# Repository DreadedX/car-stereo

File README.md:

# Peugeot 207 Bluetooth music receiver
My Peugeot has bluetooth, but only for calling.
This project aims to build a bluetooth receiver to attached to the aux in in the glovebox.

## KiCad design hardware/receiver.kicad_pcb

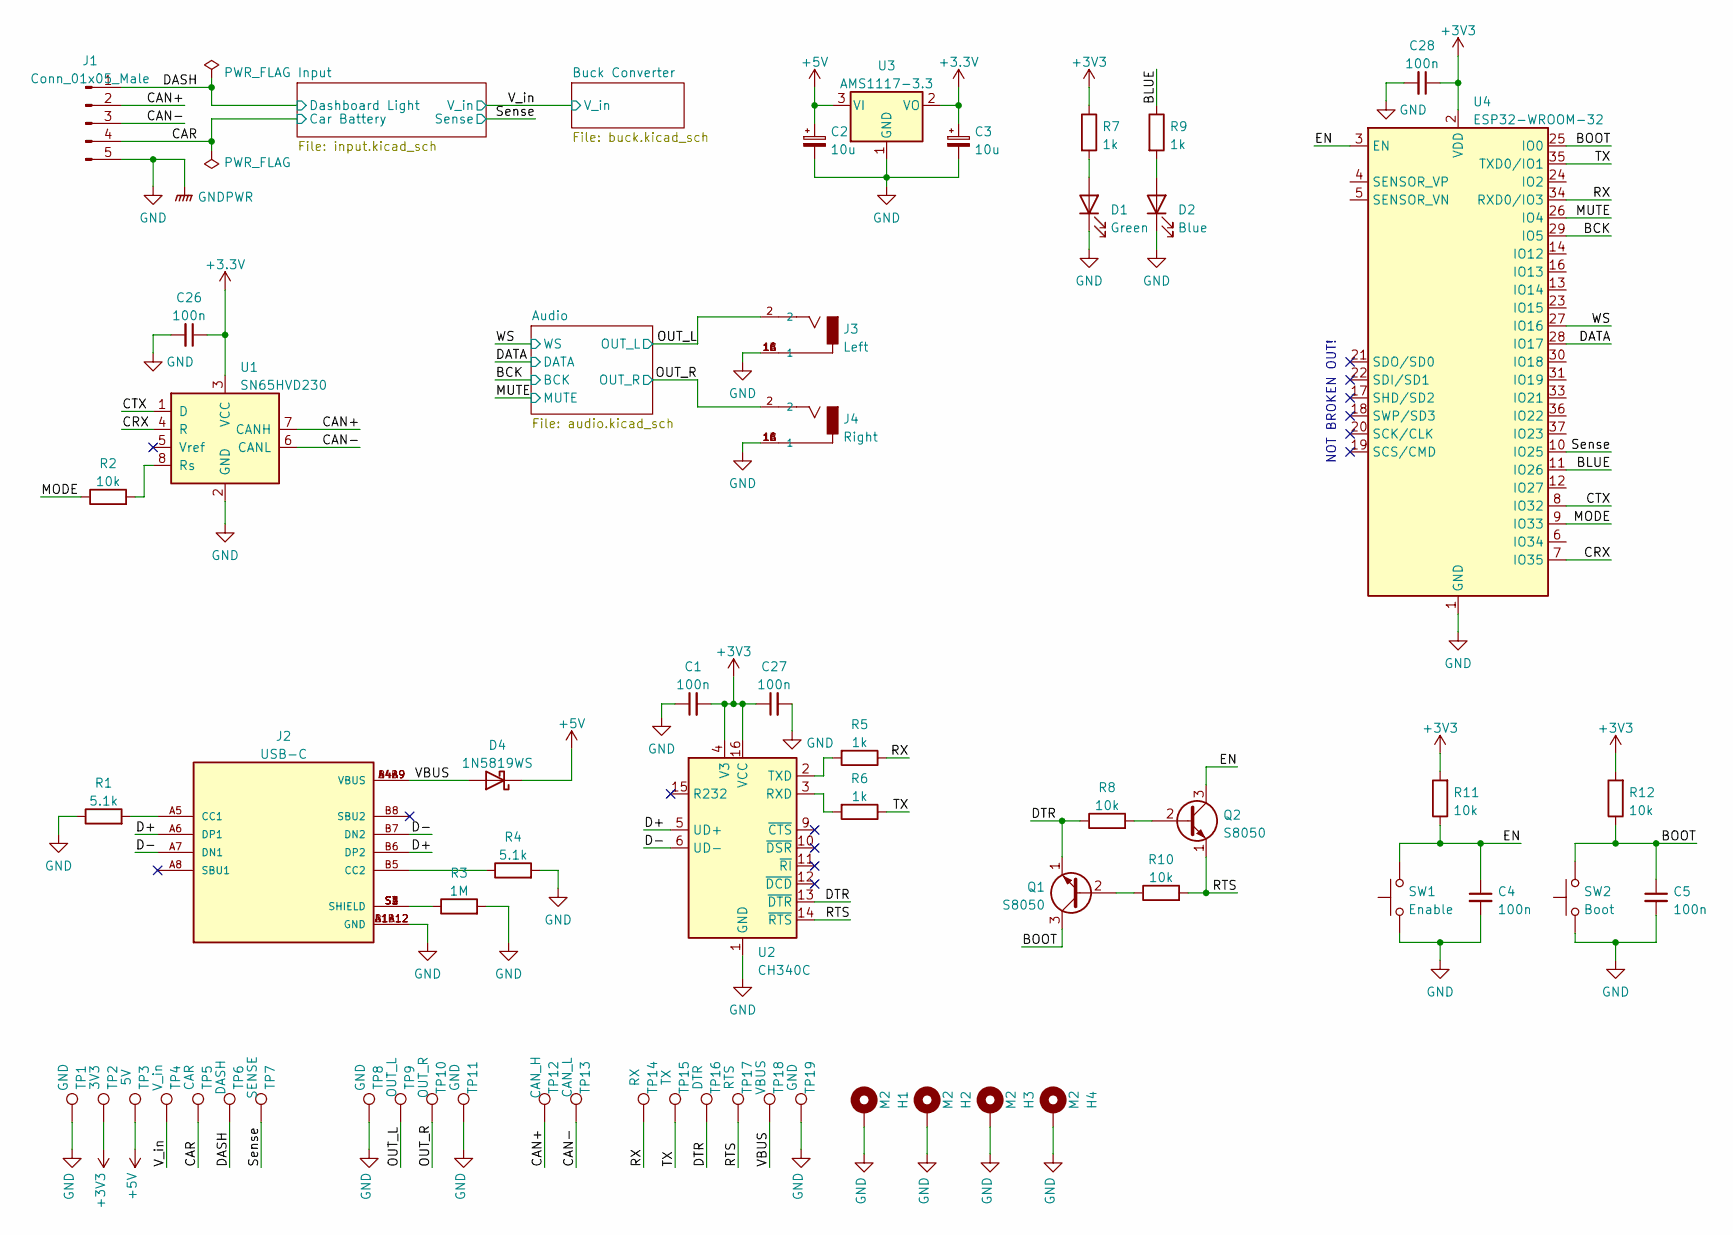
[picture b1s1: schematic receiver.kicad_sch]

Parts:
C1, C4, C5, C26, C27, C28: 100n; C_0402_1005Metric; LCSC# C1525
C2, C3: 10u; C_1206_3216Metric; LCSC# C7171
D1: Green; LED_0603_1608Metric; LCSC# C72043
D2: Blue; LED_0603_1608Metric; LCSC# C72041
D4: 1N5819WS; D_SOD-323; LCSC# C191023
H1, H2, H3, H4: M2; MountingHole_2.2mm_M2_ISO14580_Pad
J1: Conn_01x05_Male; JST_XH_S5B-XH-A-1_1x05_P2.50mm_Horizontal
J2: USB-C; HRO_TYPE-C-31-M-12; PARTREV A; LCSC# C165948
J3: Left; CUI_RCJ-013; PART_REV B
J4: Right; CUI_RCJ-013; PART_REV B
Q1, Q2: S8050; SOT-23; LCSC# C2146
R1, R4: 5.1k; R_0402_1005Metric; LCSC# C25905
R2, R8, R10, R11, R12: 10k; R_0402_1005Metric; LCSC# C25744
R3: 1M; R_0402_1005Metric; LCSC# C26083
R5, R6, R7, R9: 1k; R_0402_1005Metric; LCSC# C11702
SW1: Enable; SW_SPST_SKQG_WithStem
SW2: Boot; SW_SPST_SKQG_WithStem
TP1, TP8, TP11, TP19: GND; TestPoint_Pad_D1.0mm
TP2: 3V3; TestPoint_Pad_D1.0mm
TP3: 5V; TestPoint_Pad_D1.0mm
TP4: V_in; TestPoint_Pad_D1.0mm
TP5: CAR; TestPoint_Pad_D1.0mm
TP6: DASH; TestPoint_Pad_D1.0mm
TP7: SENSE; TestPoint_Pad_D1.0mm
TP9: OUT_L; TestPoint_Pad_D1.0mm
TP10: OUT_R; TestPoint_Pad_D1.0mm
TP12: CAN_H; TestPoint_Pad_D1.0mm
TP13: CAN_L; TestPoint_Pad_D1.0mm
TP14: RX; TestPoint_Pad_D1.0mm
TP15: TX; TestPoint_Pad_D1.0mm
TP16: DTR; TestPoint_Pad_D1.0mm
TP17: RTS; TestPoint_Pad_D1.0mm
TP18: VBUS; TestPoint_Pad_D1.0mm
U1: SN65HVD230; SOIC-8_3.9x4.9mm_P1.27mm; LCSC# C12084
U2: CH340C; SOIC-16_3.9x9.9mm_P1.27mm; LCSC# C84681
U3: AMS1117-3.3; SOT-223-3_TabPin2; LCSC# C6186
U4: ESP32-WROOM-32; LCSC# C95209

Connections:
/BCK: U4.29 (IO5); also elsewhere on the board
/BLUE: R9.1, U4.11 (IO26)
/BOOT: C5.1, Q1.3 (C), R12.1, SW2.2, U4.25 (IO0)
/CAN+: J1.2, TP12.1, U1.7 (CANH)
/CAN-: J1.3, TP13.1, U1.6 (CANL)
/CRX: U1.4 (R), U4.7 (IO35)
/CTX: U1.1 (D), U4.8 (IO32)
/D+: J2.A6 (DP1), J2.B6 (DP2), U2.5 (UD+)
/D-: J2.A7 (DN1), J2.B7 (DN2), U2.6 (UD-)
/DASH: J1.1, TP6.1; also elsewhere on the board
/DATA: U4.28 (IO17); also elsewhere on the board
/DTR: Q1.1 (E), R8.1, TP16.1, U2.13 (~DTR)
/EN: C4.1, Q2.3 (C), R11.1, SW1.2, U4.3 (EN)
/MODE: R2.1, U4.9 (IO33)
/MUTE: U4.26 (IO4); also elsewhere on the board
/OUT_L: J3.2, TP9.1; also elsewhere on the board
/OUT_R: J4.2, TP10.1; also elsewhere on the board
/RTS: Q2.1 (E), R10.2, TP17.1, U2.14 (~RTS)
/RX: R5.1, TP14.1, U4.34 (RXD0/IO3)
/Sense: TP7.1, U4.10 (IO25); also elsewhere on the board
/TX: R6.1, TP15.1, U4.35 (TXD0/IO1)
/V_in: TP4.1; also elsewhere on the board
/WS: U4.27 (IO16); also elsewhere on the board
GND: C1.1, C2.2, C3.2, C4.2, C5.2, C26.2, C27.2, C28.2, D1.1 (K), D2.1 (K), H1.1, H2.1, H3.1, H4.1, J1.5, J2.A1B12 (GND), J2.B1A12 (GND), J3.1A (1), J3.1B (1), J3.1C (1), J4.1A (1), J4.1B (1), J4.1C (1), R1.1, R3.2, R4.2, SW1.1, SW2.1, TP1.1, TP8.1, TP11.1, TP19.1, U1.2 (GND), U2.1 (GND), U3.1 (GND), U4.1 (GND), U4.15 (GND), U4.38 (GND), U4.39 (GND); also elsewhere on the board
unnamed: D1.2 (A), R7.2
unnamed: D2.2 (A), R9.2
unnamed: J2.A5 (CC1), R1.2
unnamed: J2.B5 (CC2), R4.1
unnamed: J2.S1 (SHIELD), J2.S2 (SHIELD), J2.S3 (SHIELD), J2.S4 (SHIELD), R3.1
unnamed: Q1.2 (B), R10.1
unnamed: Q2.2 (B), R8.2
unnamed: R2.2, U1.8 (Rs)
unnamed: R6.2, U2.3 (RXD)
unnamed: R5.2, U2.2 (TXD)

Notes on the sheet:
NOT BROKEN OUT!

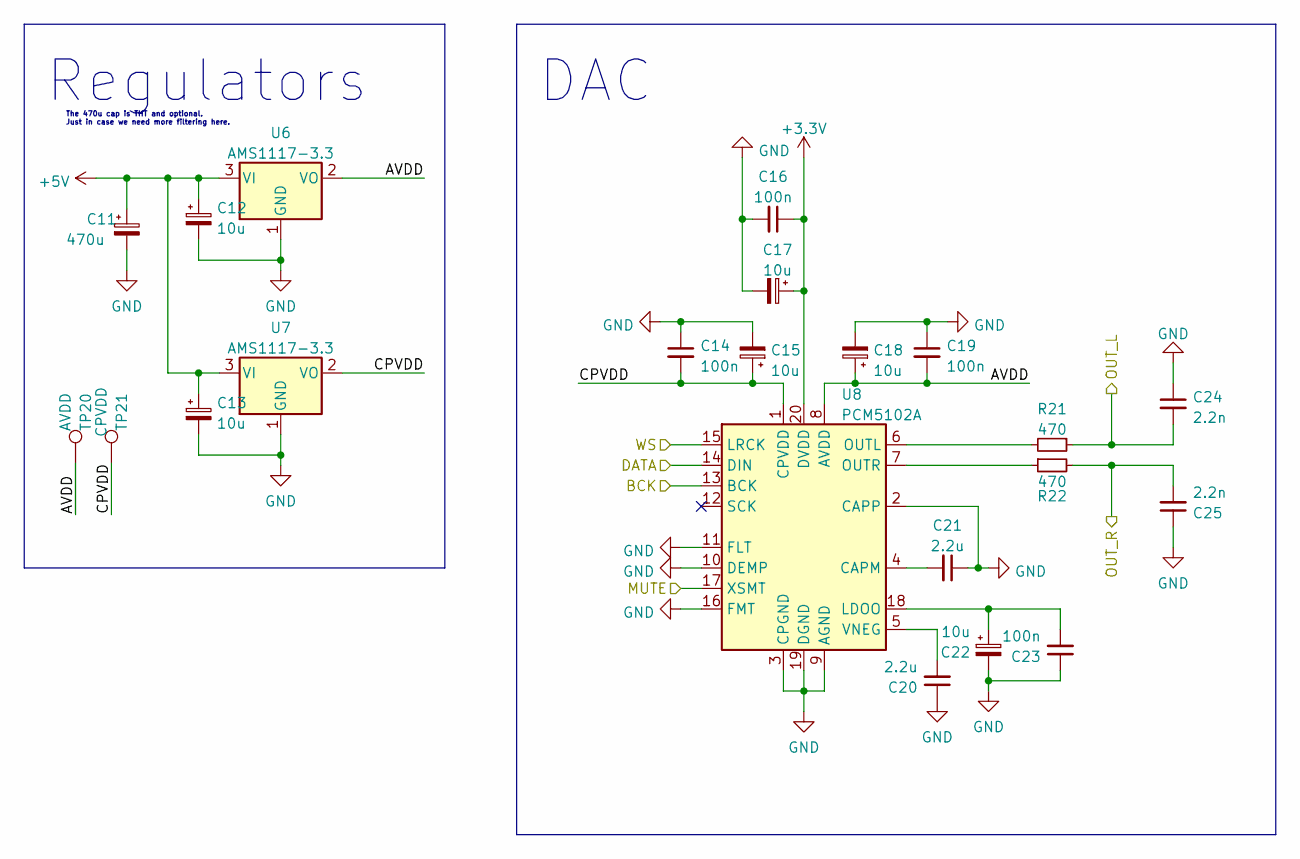
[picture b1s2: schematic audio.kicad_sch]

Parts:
C11: 470u; CP_Radial_D5.0mm_P2.50mm
C12, C13, C15, C17, C18, C22: 10u; C_1206_3216Metric; LCSC# C7171
C14, C16, C19, C23: 100n; C_0402_1005Metric; LCSC# C1525
C20, C21: 2.2u; C_0402_1005Metric; LCSC# C12530
C24, C25: 2.2n; C_0402_1005Metric; LCSC# C1531
R21, R22: 470; R_0402_1005Metric; LCSC# C25117
TP20: AVDD; TestPoint_Pad_D1.0mm
TP21: CPVDD; TestPoint_Pad_D1.0mm
U6, U7: AMS1117-3.3; SOT-223-3_TabPin2; LCSC# C6186
U8: PCM5102A; TSSOP-20_4.4x6.5mm_P0.65mm; LCSC# C107671

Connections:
/Audio/AVDD: C18.1, C19.2, TP20.1, U6.2 (VO), U8.8 (AVDD)
/Audio/CPVDD: C14.2, C15.1, TP21.1, U7.2 (VO), U8.1 (CPVDD)
/BCK: U8.13 (BCK); also elsewhere on the board
/DATA: U8.14 (DIN); also elsewhere on the board
/MUTE: U8.17 (XSMT); also elsewhere on the board
/OUT_L: C24.2, R21.1; also elsewhere on the board
/OUT_R: C25.2, R22.2; also elsewhere on the board
/WS: U8.15 (LRCK); also elsewhere on the board
GND: C11.2, C12.2, C13.2, C14.1, C15.2, C16.2, C17.2, C18.2, C19.1, C20.1, C21.1, C22.2, C23.1, C24.1, C25.1, U6.1 (GND), U7.1 (GND), U8.2 (CAPP), U8.3 (CPGND), U8.9 (AGND), U8.10 (DEMP), U8.11 (FLT), U8.16 (FMT), U8.19 (DGND); also elsewhere on the board
unnamed: C21.2, U8.4 (CAPM)
unnamed: C22.1, C23.2, U8.18 (LDOO)
unnamed: R21.2, U8.6 (OUTL)
unnamed: R22.1, U8.7 (OUTR)
unnamed: C20.2, U8.5 (VNEG)

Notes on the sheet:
The 470u cap is THT and optional. Just in case we need more filtering here.
Regulators
DAC

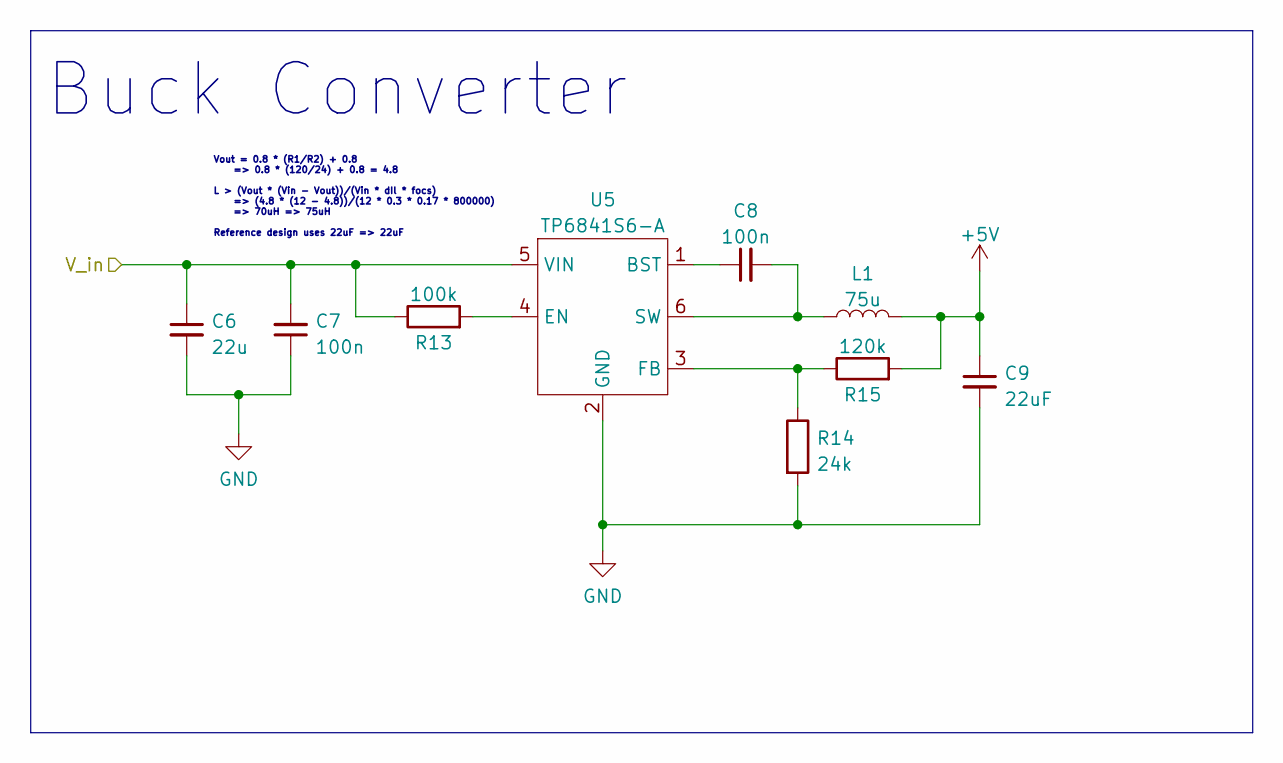
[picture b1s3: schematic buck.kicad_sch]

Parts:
C6: 22u; C_1206_3216Metric; LCSC# C12891
C7, C8: 100n; C_0402_1005Metric; LCSC# C1525
C9: 22uF; C_0603_1608Metric; LCSC# C59461
L1: 75u; IND-SMD_L4.0-W4.0_FNR40XXS; LCSC# C167848
R13: 100k; R_0402_1005Metric; LCSC# C25741
R14: 24k; R_0402_1005Metric; LCSC# C25769
R15: 120k; R_0402_1005Metric; LCSC# C25750
U5: TP6841S6-A; SOT-23-6; LCSC# C2844924

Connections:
/V_in: C6.1, C7.2, R13.1, U5.5 (VIN); also elsewhere on the board
GND: C6.2, C7.1, C9.2, R14.2, U5.2 (GND); also elsewhere on the board
unnamed: C8.1, U5.1 (BST)
unnamed: R13.2, U5.4 (EN)
unnamed: R14.1, R15.1, U5.3 (FB)
unnamed: C8.2, L1.1, U5.6 (SW)

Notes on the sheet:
Buck Converter
Vout = 0.8 * (R1/R2) + 0.8 => 0.8 * (120/24) + 0.8 = 4.8 L > (Vout * (Vin - Vout))/(Vin * dIl * focs) => (4.8 * (12 - 4.8))/(12 * 0.3 * 0.17 * 800000) => 70uH => 75uH Reference design uses 22uF => 22uF

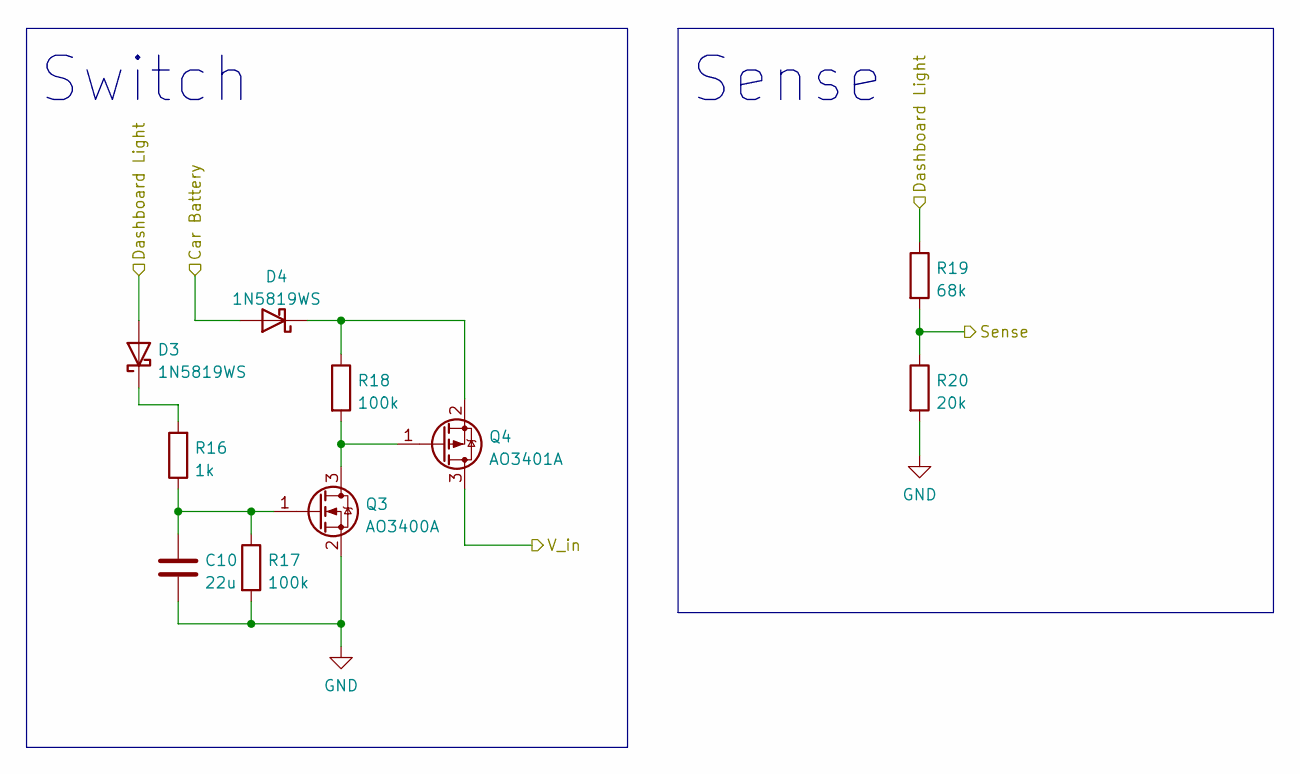
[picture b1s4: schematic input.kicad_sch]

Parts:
C10: 22u; C_1206_3216Metric; LCSC# C12891
D3, D4: 1N5819WS; D_SOD-323; LCSC# C191023
Q3: AO3400A; SOT-23; LCSC# C20917
Q4: AO3401A; SOT-23; LCSC# C15127
R16: 1k; R_0402_1005Metric; LCSC# C11702
R17, R18: 100k; R_0402_1005Metric; LCSC# C25741
R19: 68k; R_0402_1005Metric; LCSC# C36871
R20: 20k; R_0402_1005Metric; LCSC# C25765

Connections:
/DASH: D3.2 (A), R19.1; also elsewhere on the board
/Sense: R19.2, R20.1; also elsewhere on the board
/V_in: Q4.3 (D); also elsewhere on the board
GND: C10.2, Q3.2 (S), R17.2, R20.2; also elsewhere on the board
unnamed: D3.1 (K), R16.2
unnamed: Q3.3 (D), Q4.1 (G), R18.2
unnamed: C10.1, Q3.1 (G), R16.1, R17.1

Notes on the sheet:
Switch
Sense

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
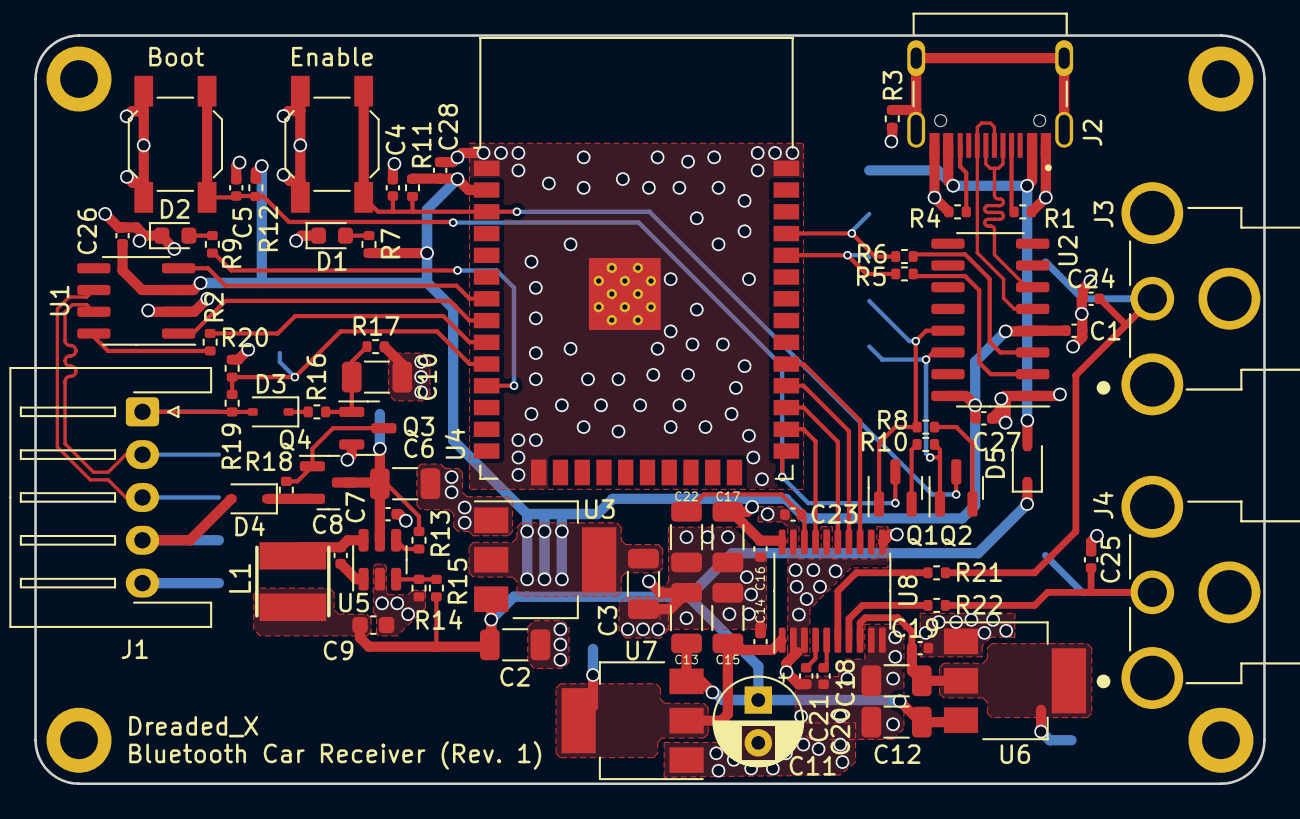
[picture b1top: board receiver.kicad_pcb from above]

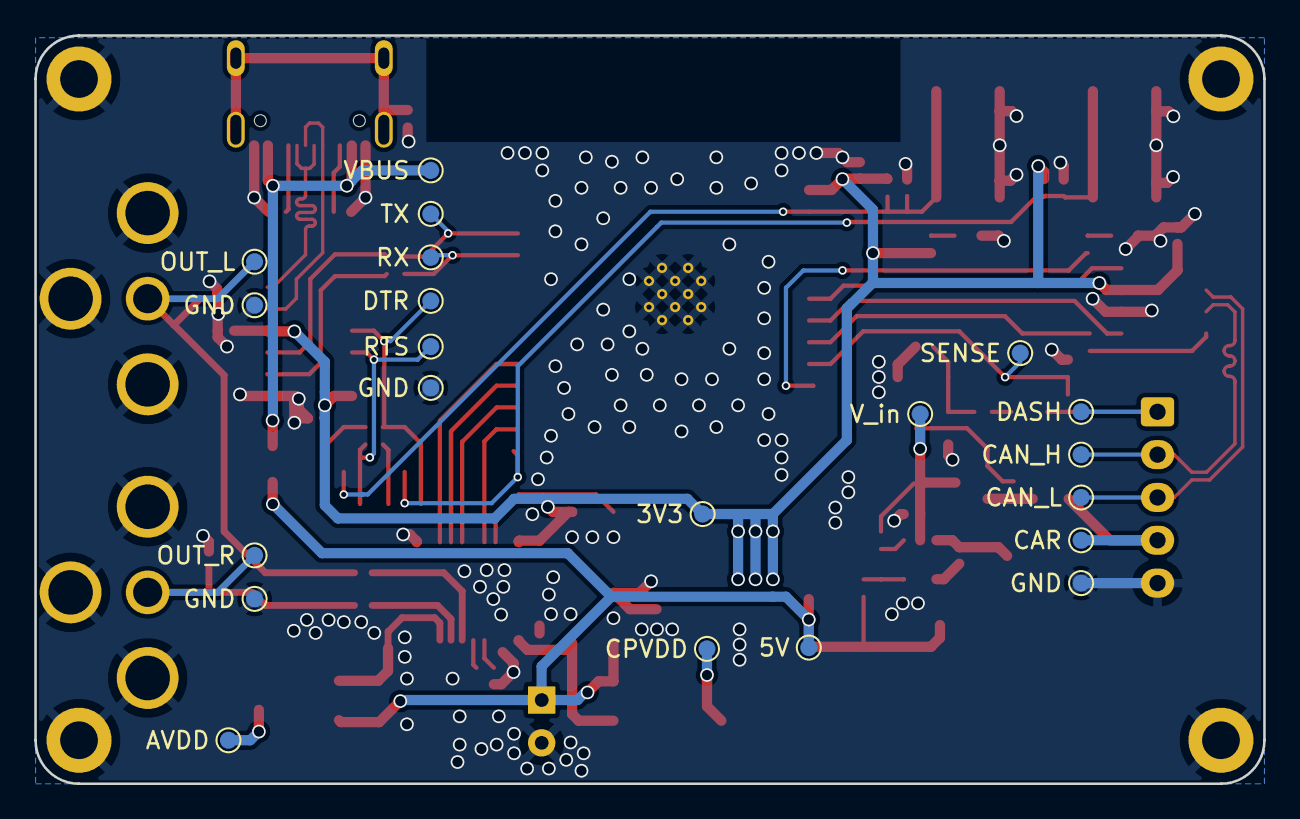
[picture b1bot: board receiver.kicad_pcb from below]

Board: 2 copper layers, 71.8 x 43.7 mm, 99 parts (21 on the bottom side), 53 nets.

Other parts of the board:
D5: 1N5819WS; D_SOD-323

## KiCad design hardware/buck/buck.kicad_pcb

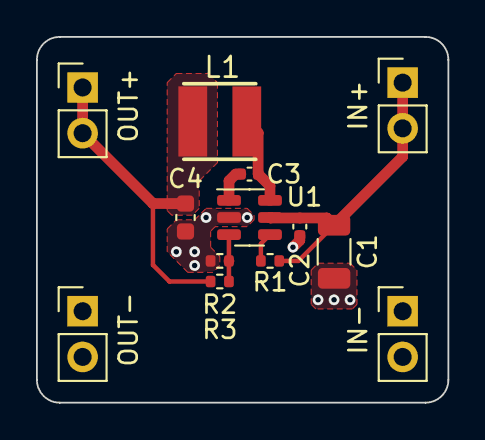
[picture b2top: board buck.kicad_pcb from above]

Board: 2 copper layers, 22.9 x 20.3 mm, 13 parts (0 on the bottom side), 7 nets.

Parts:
C1: 22u; C_1206_3216Metric
C2, C3: 100n; C_0402_1005Metric
C4: 22uF; C_0603_1608Metric
J1: IN+; PinHeader_1x02_P2.54mm_Vertical
J2: IN-; PinHeader_1x02_P2.54mm_Vertical
J3: OUT+; PinHeader_1x02_P2.54mm_Vertical
J4: OUT-; PinHeader_1x02_P2.54mm_Vertical
L1: 75u; IND-SMD_L4.0-W4.0_FNR40XXS
R1: 100k; R_0402_1005Metric
R2: 24k; R_0402_1005Metric
R3: 120k; R_0402_1005Metric
U1: TP6841S6-A; SOT-23-6

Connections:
+5V: C4.1, J3.1, J3.2, L1.2, R3.2
GND: C1.2, C2.1, C4.2, J2.1, J2.2, J4.1, J4.2, R2.2, U1.2 (GND)
unnamed: C3.1, U1.1 (BST)
unnamed: C3.2, L1.1, U1.6 (SW)
unnamed: R1.2, U1.4 (EN)
unnamed: R2.1, R3.1, U1.3 (FB)
Vin: C1.1, C2.2, J1.1, J1.2, R1.1, U1.5 (VIN)

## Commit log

2022-05-20 Refactored and removed unneeded parts
2022-05-20 Reorganized project
2022-05-21 Removed set/get volume as we are not going to use it for now
2022-05-21 Added basis for hardware design
2022-05-22 Worked on schematics and added some parts
2022-05-23 Moved esp-idf to tagged version
2022-05-23 Revert "Moved esp-idf to tagged version"
    This reverts commit c292934bb0d6cd906664b3d37ffbb895e47d116f.
2022-05-25 Fixed: Not set to discoverable if there is no last device
2022-05-26 Worked on schematic and split parts into seperate schematics
2022-05-26 Make sure we include everything in the pick and place files
2022-05-26 Put buck converter on seperate PCB for validation
2022-05-26 Created falstad circuit simulation for the input power switch
2022-05-26 Started work on a companion app to read out things like battery life
2022-05-26 Moved software into seperate folder
2022-06-09 Fixed flipped transistor
2022-06-09 Wrote CAN Bus data visualizer
2022-06-09 Canmonitor was not fast enough
2022-06-11 Started work on CAN bus
2022-06-11 Fixed accessing out of scope memory
2022-06-13 Implemented CAN Bus listening
2022-06-13 Play/pause using the forward button on the steering wheel
2022-06-14 Implemented forward and backward
2022-06-14 Refactored and current playstatus is now received from device
2022-06-14 Forgot to store previous button state
2022-06-15 Volume is now synced from car to phone
2022-06-15 Some small tweaks
2022-06-15 MultiPurposeButton now uses a timer to time the long and short press
2022-06-15 Refactor and small optimization
2022-06-15 Turned on O2
2022-06-15 Fixed bugs
2022-06-15 Buttons should now only work if we are on AUX2
2022-06-16 Seek forward and backward using scroll wheel in car
2022-06-16 Only listen for buttons to prevent weird issues from occuring
2022-06-16 Swapped forward and backwards on scroll made scroll larger
2022-06-20 Started work on using TWAI instead of external CAN bus
2022-06-21 Reduced some logging, and added id filter
2022-06-22 Fixed mask and made buttons functional again
2022-06-23 Removed MCP2515 code as it is no longer required
2022-06-23 Added auto pausing under certain circumstances
2022-06-24 Forgot to remove can.h from main.cpp
2022-06-24 Added proof of concept to control volume
2022-06-28 Revamped how volume changes are handled to also support remote volume control
2022-06-28 Fixed some issues
2022-06-29 Adjusted volume curve, only change volume if enabled and added option to cancel volume sync
2022-06-29 Went back to linear volume curve
2022-07-03 Small tweaks to hopefully improve performance
2022-07-04 Audio data now goes through a ringbuffer first so we can hopefully smooth out the sequence number errors
2022-07-07 Removed unnecessary includes
2022-07-07 Alternative power input switch system
2022-07-07 Finished first iteration of the PCB
2022-07-07 Removed app
2022-07-07 Made corners rounded and added mounting holes
2022-07-07 Configured thermal reliefs for mounting holes
2022-09-29 Moved pin config into seperate config file
2022-09-29 Added pin config for production
2023-03-31 Updated to new version of KiCad and made some small changes to the design
2023-04-01 Added menuconfig option to switch between prototype and eventual production hardware
2023-04-01 Renamed NVS namespace
2023-04-01 Added led to indicate bluetooth status
2023-04-01 Little bit of clean up
